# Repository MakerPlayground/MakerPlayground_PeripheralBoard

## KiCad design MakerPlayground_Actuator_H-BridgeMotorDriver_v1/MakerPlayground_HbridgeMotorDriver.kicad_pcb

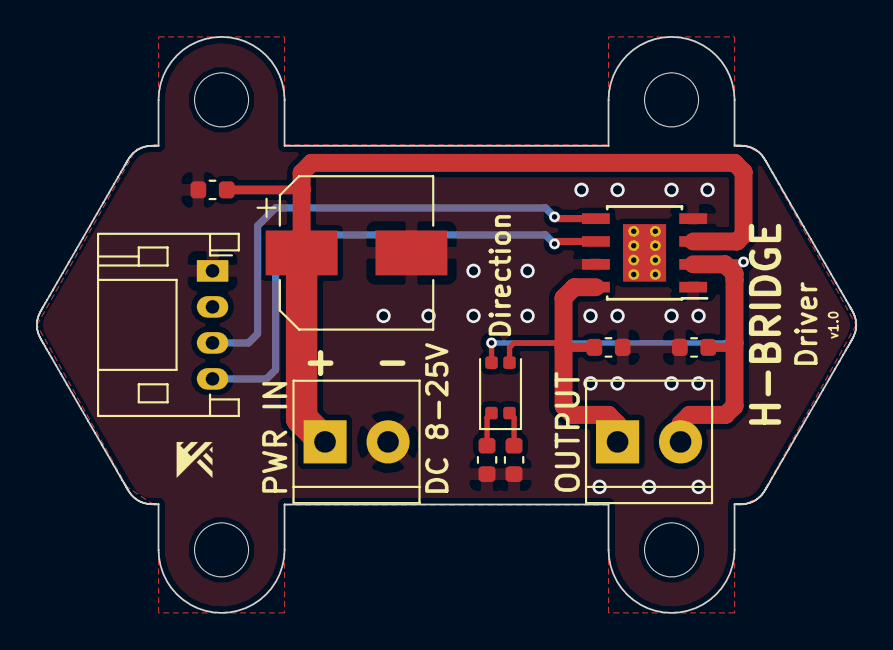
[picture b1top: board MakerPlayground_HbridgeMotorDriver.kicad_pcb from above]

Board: 2 copper layers, 45.5 x 32.0 mm, 11 parts (0 on the bottom side), 8 nets.

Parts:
C1, C2, C3: 0.1uF; C_0603_1608Metric
C4: 100uF; CP_Elec_8x5.4
D1: LED_Dual_CCAA; LED_1206_3216Metric_AAKK
J1: Conn_01x04; JST_PH_S4B-PH-K_1x04_P2.00mm_Horizontal
J2, J3: Screw_Terminal_01x02; TerminalBlock_Dinkle_ED350V_1x02_P3.50mm_Horizontal
R1, R2: 1k; R_0603_1608Metric
U1: ROHM_BD62110AEFJ; HTSOP-8-1EP_3.9x4.9mm_P1.27mm_ThermalVias

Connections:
GND: C1.2, C2.2, C3.2, C4.2, J1.1, J3.2, R1.1, R2.1, U1.1, U1.4, U1.7
IN1: J1.3, U1.5
IN2: J1.4, U1.6
unnamed: D1.1, R1.2
unnamed: D1.2, R2.2
OUT1: C1.1, D1.3, J2.2, U1.2
OUT2: C2.1, D1.4, J2.1, U1.8
VCC: C3.1, C4.1, J3.1, U1.3

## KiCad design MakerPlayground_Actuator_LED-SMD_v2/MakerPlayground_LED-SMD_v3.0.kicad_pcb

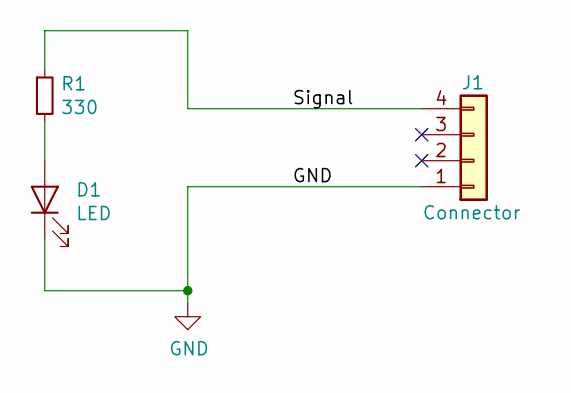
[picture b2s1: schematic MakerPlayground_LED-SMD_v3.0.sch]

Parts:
D1: LED; LED_0603
J1: Connector; JST_PH_S4B-PH-SM4-TB_1x04-1MP_P2.00mm_Horizontal
R1: 330; R_0603_1608Metric

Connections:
/Signal: J1.4, R1.1
GND: D1.1 (K), J1.1
unnamed: D1.2 (A), R1.2

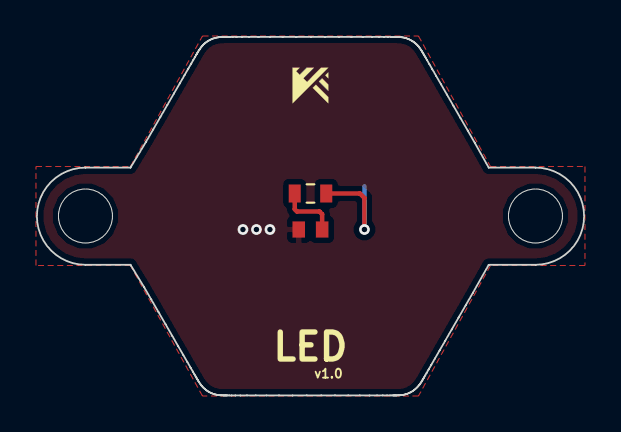
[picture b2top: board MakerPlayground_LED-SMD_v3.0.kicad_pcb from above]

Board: 2 copper layers, 30.4 x 19.9 mm, 3 parts (1 on the bottom side), 3 nets.

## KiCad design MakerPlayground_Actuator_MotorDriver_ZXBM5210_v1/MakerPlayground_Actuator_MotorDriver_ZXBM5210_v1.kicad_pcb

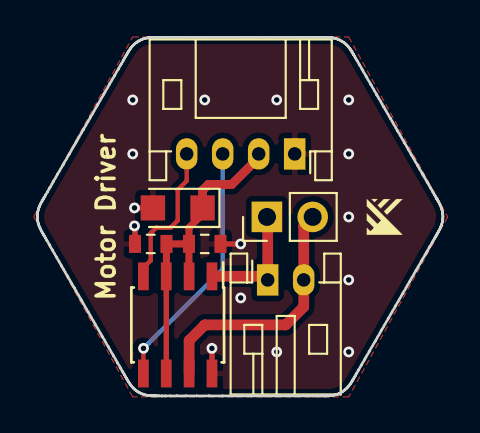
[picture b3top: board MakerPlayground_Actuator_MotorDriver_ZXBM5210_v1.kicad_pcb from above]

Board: 2 copper layers, 22.5 x 19.9 mm, 7 parts (0 on the bottom side), 6 nets.

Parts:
C1, C2: 1uF; C_0603_1608Metric
C3: 22uF; CP_EIA-3216-12_Kemet-S
J1: Conn_01x04; JST_PH_S4B-PH-K_1x04_P2.00mm_Horizontal
J2: Conn_01x02; JST_PH_S2B-PH-K_1x02_P2.00mm_Horizontal
J3: Conn_01x02; PinHeader_1x02_P2.54mm_Vertical
U1: Diodes_ZXBM5210; SOIC-8_3.9x4.9mm_P1.27mm

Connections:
GND: C1.2, C2.2, C3.2, J1.1, U1.8
Mpin_1: J2.1, J3.1, U1.1
Mpin_2: J2.2, J3.2, U1.7
SIG_1: J1.4, U1.4
SIG_2: J1.3, U1.5
VCC: C1.1, C2.1, C3.1, J1.2, U1.2, U1.3, U1.6

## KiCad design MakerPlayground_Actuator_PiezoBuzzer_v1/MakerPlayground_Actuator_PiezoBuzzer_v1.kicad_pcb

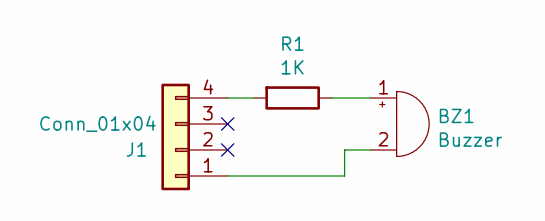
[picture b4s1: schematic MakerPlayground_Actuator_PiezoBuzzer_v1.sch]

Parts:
BZ1: Buzzer; PKM22EPPH2002-B0
J1: Conn_01x04; JST_PH_S4B-PH-SM4-TB_1x04-1MP_P2.00mm_Horizontal
R1: 1K; R_0603_1608Metric

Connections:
unnamed: BZ1.1 (-), R1.1
unnamed: BZ1.2 (+), J1.1
unnamed: J1.4, R1.2

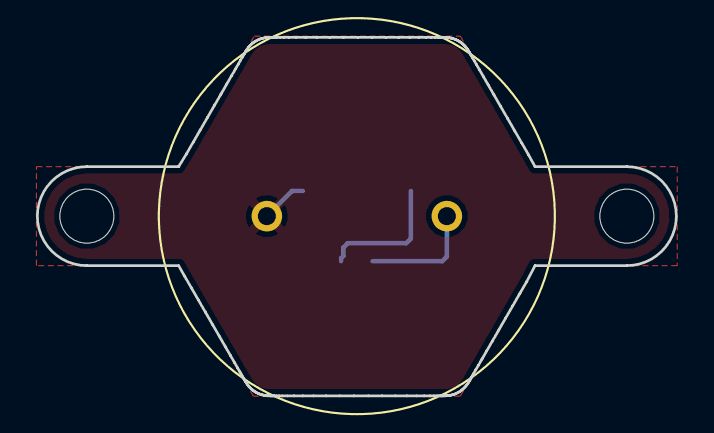
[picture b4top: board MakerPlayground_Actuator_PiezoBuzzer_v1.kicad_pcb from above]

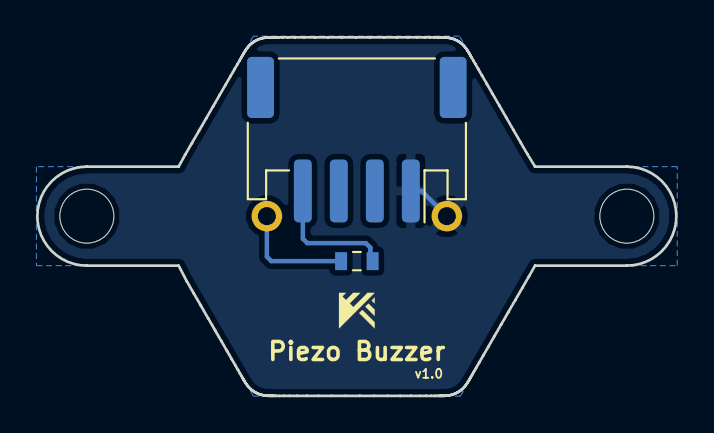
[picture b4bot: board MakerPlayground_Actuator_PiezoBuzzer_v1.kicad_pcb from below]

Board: 2 copper layers, 35.5 x 19.9 mm, 3 parts (2 on the bottom side), 3 nets.

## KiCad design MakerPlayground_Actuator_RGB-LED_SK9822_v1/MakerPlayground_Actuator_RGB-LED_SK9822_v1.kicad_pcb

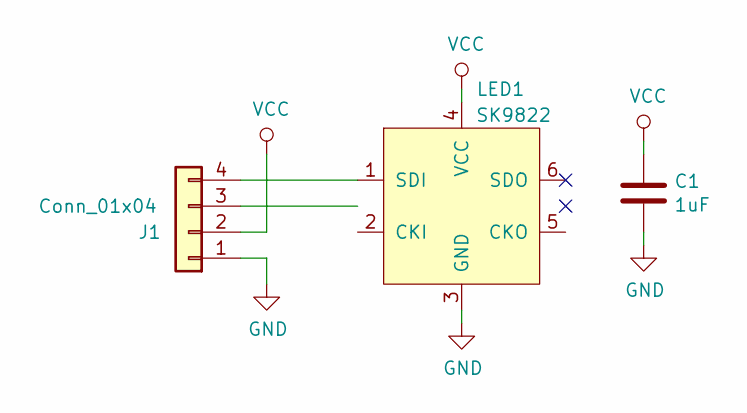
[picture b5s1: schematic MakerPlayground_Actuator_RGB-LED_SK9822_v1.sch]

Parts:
C1: 1uF; C_0603_1608Metric
J1: Conn_01x04; JST_PH_S4B-PH-K_1x04_P2.00mm_Horizontal
LED1: SK9822

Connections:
GND: C1.2, J1.1, LED1.3 (GND)
unnamed: J1.3, LED1.2 (CKI)
unnamed: J1.4, LED1.1 (SDI)
VCC: C1.1, J1.2, LED1.4 (VCC)

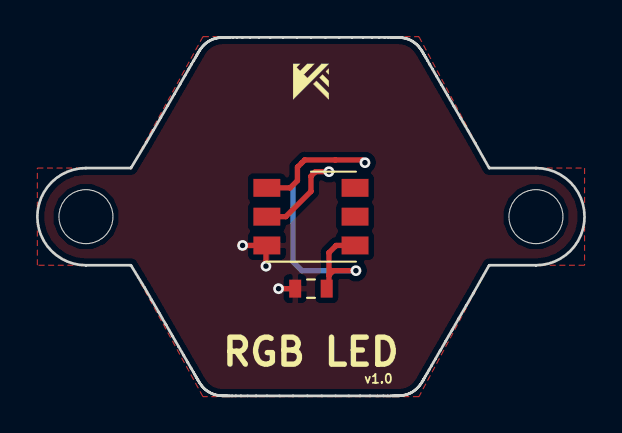
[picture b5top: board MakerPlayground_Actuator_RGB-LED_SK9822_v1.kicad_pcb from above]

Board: 2 copper layers, 30.4 x 19.9 mm, 3 parts (1 on the bottom side), 4 nets.

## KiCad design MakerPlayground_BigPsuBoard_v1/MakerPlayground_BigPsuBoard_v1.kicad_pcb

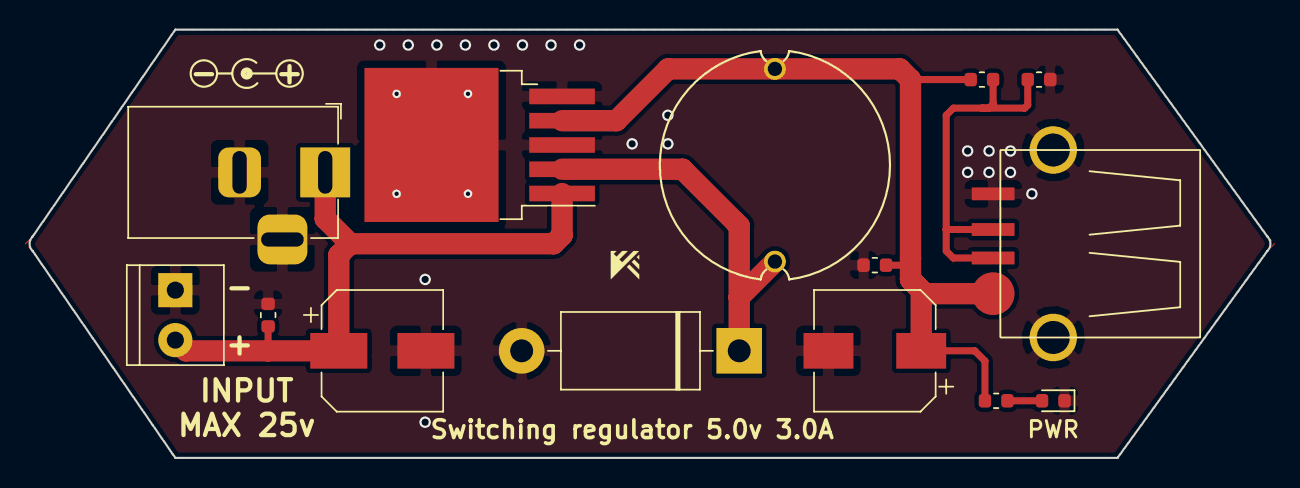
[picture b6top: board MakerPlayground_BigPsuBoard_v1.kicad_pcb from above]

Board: 2 copper layers, 86.9 x 30.0 mm, 14 parts (0 on the bottom side), 6 nets.

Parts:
C1, C3: 0.1uF; C_0603_1608Metric
C2: 100uF; CP_Elec_8x5.4
C4: 1000uF; CP_Elec_8x10
D1: 1N5822; D_DO-201AD_P15.24mm_Horizontal
D2: LED; LED_0603_1608Metric
J1: Barrel_Jack_Switch; BarrelJack_Horizontal
J2: USB_A; USB-A-S-NOSILK-FEMALE
J3: Screw_Terminal_01x02; TerminalBlock_Dinkle_ED350V_1x02_P3.50mm_Horizontal
L1: 100uH; SAGAMI_7916N_L-Radial_D16.00_P13.50
R1, R2, R3: 1k; R_0603_1608Metric
U1: LM2576S-5; TO-263-5_TabPin3

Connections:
Data: J2.2, J2.3, R2.2, R3.1
GND: C1.2, C2.2, C3.2, C4.2, D1.2, D2.1, J1.2, J1.3, J2.4, J3.1, R3.2, U1.3, U1.5
unnamed: C1.1, C2.1, J1.1, J3.2, U1.1
unnamed: D1.1, L1.1, U1.2
unnamed: D2.2, R1.2
Vout: C3.1, C4.1, J2.1, L1.2, R1.1, R2.1, U1.4

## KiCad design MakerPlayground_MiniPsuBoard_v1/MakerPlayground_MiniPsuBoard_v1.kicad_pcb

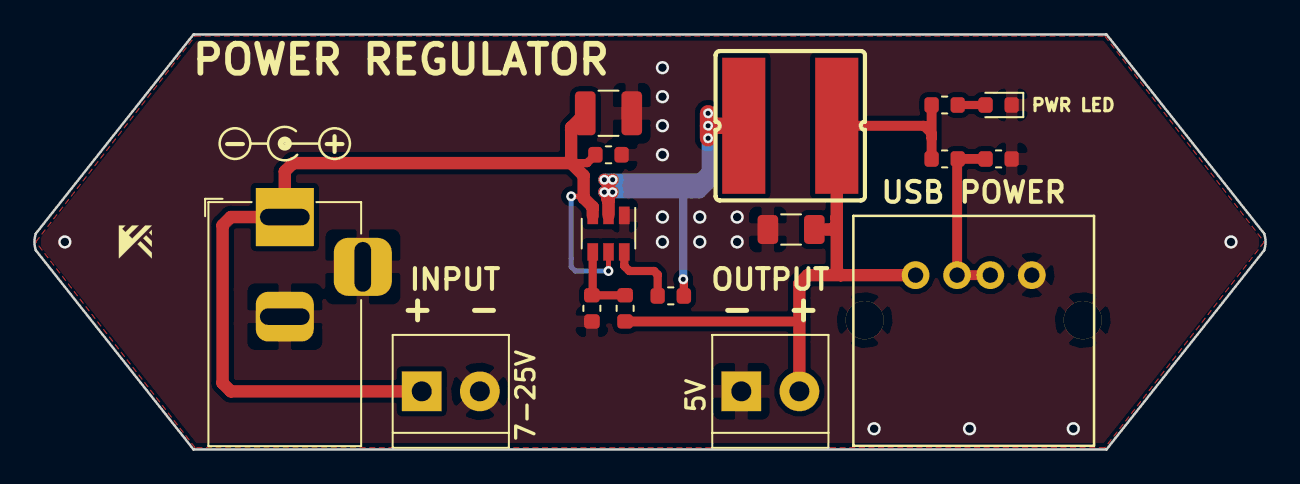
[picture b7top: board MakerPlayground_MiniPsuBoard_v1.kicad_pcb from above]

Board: 2 copper layers, 74.2 x 25.0 mm, 16 parts (0 on the bottom side), 8 nets.

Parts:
C1: 22uF; C_1210_3225Metric
C2, C4: 0.1uF; C_0603_1608Metric
C3: 47uF; C_1206_3216Metric
D1: LED; LED_0603_1608Metric
J1, J3: Screw_Terminal_01x02; TerminalBlock_Dinkle_ED350V_1x02_P3.50mm_Horizontal
J2: Barrel_Jack_Switch; BarrelJack_Horizontal
J4: USB_A; UE27-AC54-100
L1: 3.3uH; BOURNS_SRN8040
R1: 56.2k; R_0603_1608Metric
R2: 10k; R_0603_1608Metric
R3, R4, R5: 1k; R_0603_1608Metric
U1: TPS563200; SOT-23-6

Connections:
DATA: J4.2, J4.3, R3.2, R4.1
GND: C1.2, C3.2, C4.2, D1.1, J1.2, J2.2, J2.3, J3.1, J4.4, J4.5, R2.2, R4.2, U1.1
unnamed: C2.1, L1.1, U1.2
unnamed: C2.2, U1.6
unnamed: D1.2, R5.2
unnamed: R1.2, R2.1, U1.4
VIN: C1.1, C4.1, J1.1, J2.1, U1.3, U1.5
VOUT: C3.1, J3.2, J4.1, L1.2, R1.1, R3.1, R5.1

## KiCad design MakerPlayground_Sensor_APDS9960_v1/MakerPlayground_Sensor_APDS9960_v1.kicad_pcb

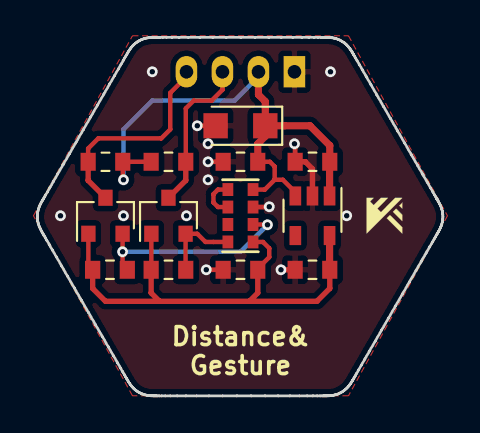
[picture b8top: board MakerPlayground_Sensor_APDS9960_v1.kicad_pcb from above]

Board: 2 copper layers, 22.5 x 19.9 mm, 14 parts (1 on the bottom side), 8 nets.

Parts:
C1, C2, C4, C5: 1uF; C_0603_1608Metric_Pad0.84x1.00mm_HandSolder
C3: 22uF; CP_EIA-3216-12_Kemet-S
J1: Connector; JST_PH_S4B-PH-K_1x04_P2.00mm_Horizontal
Q1, Q2: BSS138; SOT-23
R2, R3, R4, R5: 10k; R_0603_1608Metric_Pad0.84x1.00mm_HandSolder
U1: APDS-9960; APDS-9130
U2: AP2127K-3.3; SOT-23-5

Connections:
+3V3: C2.1, C5.1, Q1.1, Q2.1, R3.2, R5.2, U1.8, U2.5
GND: C1.2, C2.2, C3.2, C4.2, C5.2, J1.1, U1.6, U2.2
unnamed: U1.3, U1.4
SCL: J1.4, Q2.3, R4.1
SCL_S: Q2.2, R5.1, U1.7
SDA: J1.3, Q1.3, R2.1
SDA_S: Q1.2, R3.1, U1.1
VCC: C1.1, C3.1, C4.1, J1.2, R2.2, R4.2, U1.5, U2.1, U2.3
